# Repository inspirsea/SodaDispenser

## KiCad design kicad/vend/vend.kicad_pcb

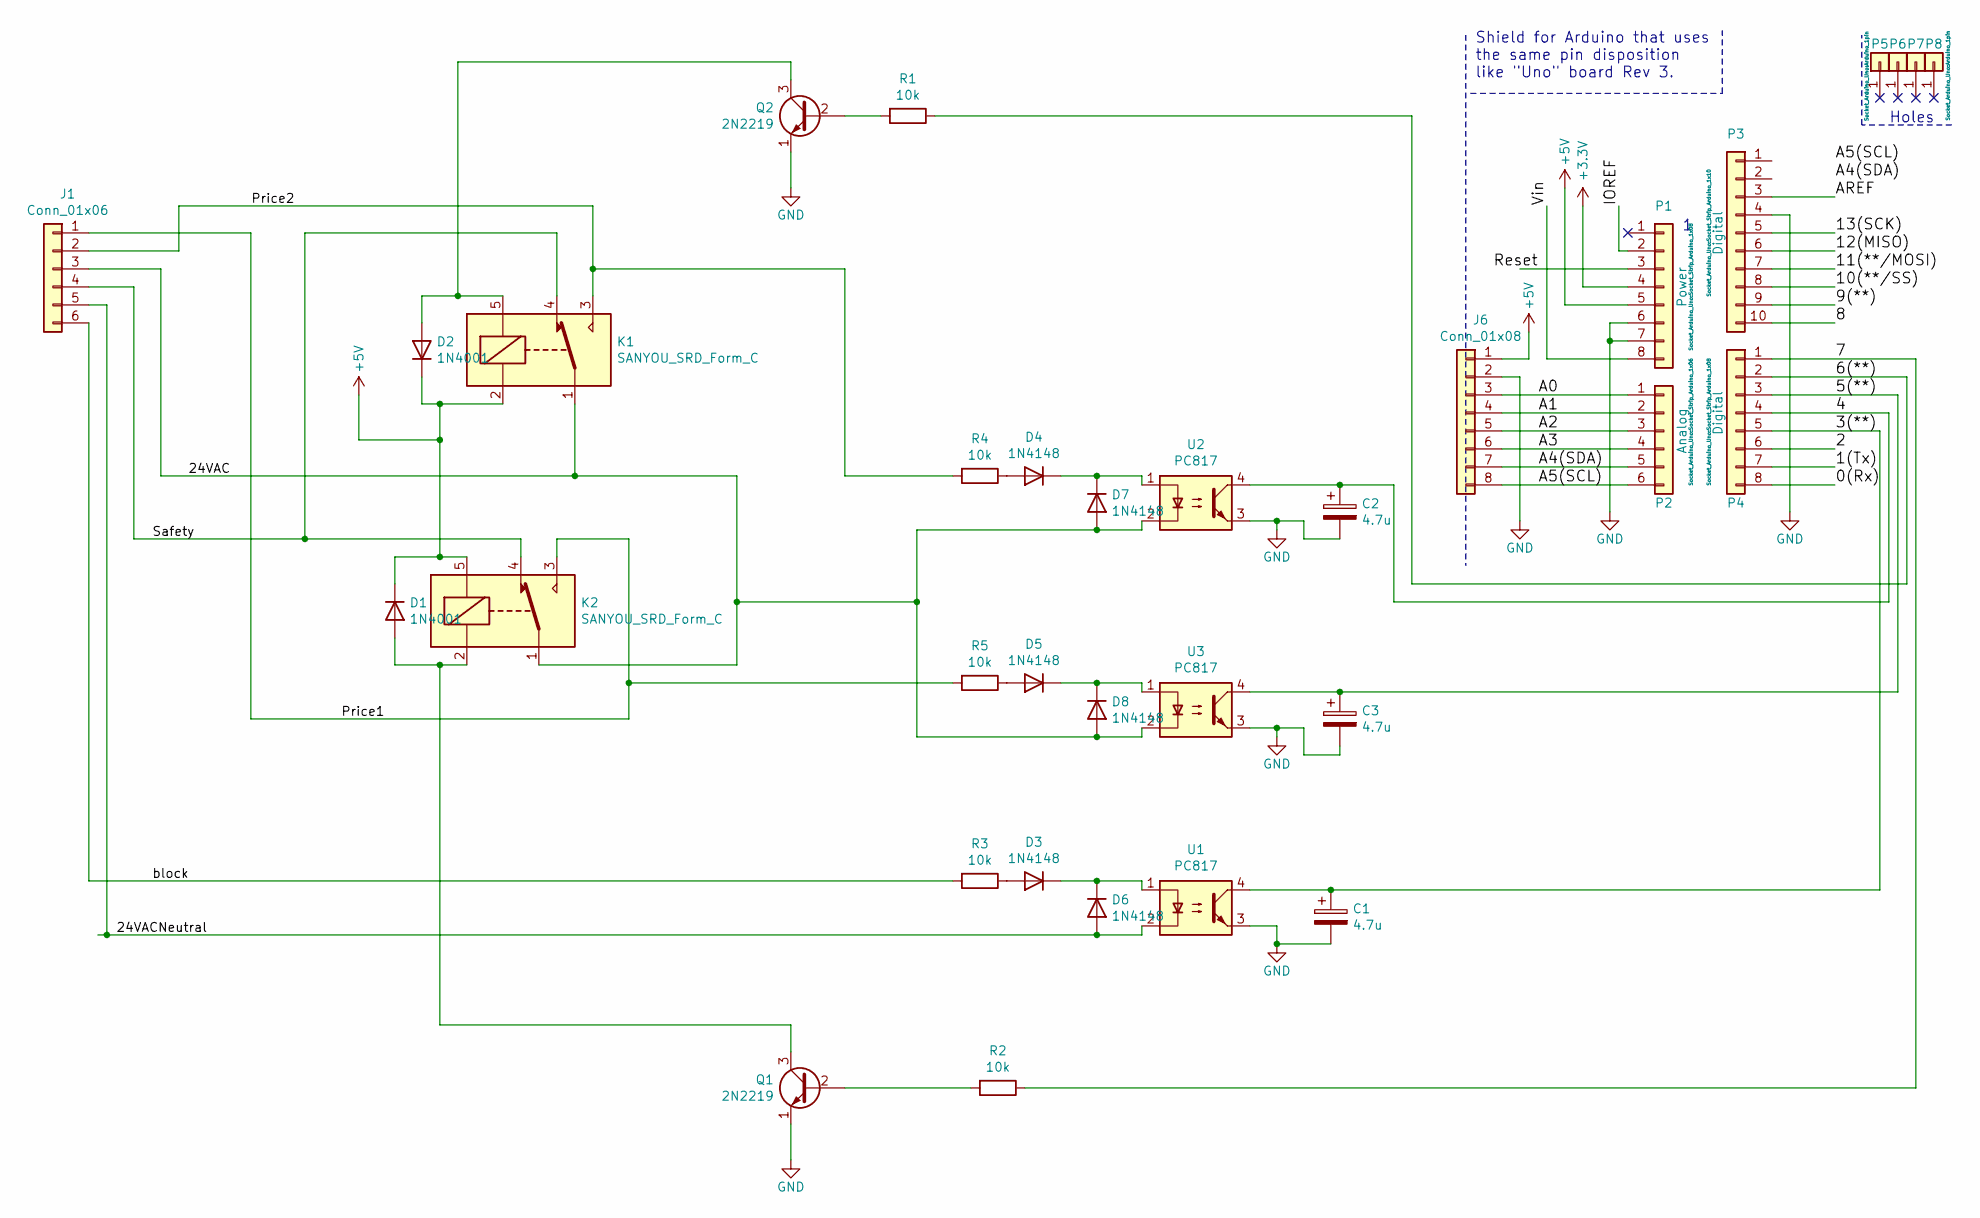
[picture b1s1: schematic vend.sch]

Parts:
C1, C2, C3: 4.7u; CP_Radial_D6.3mm_P2.50mm
D1, D2: 1N4001; D_DO-41_SOD81_P10.16mm_Horizontal
D3, D4, D5, D6, D7, D8: 1N4148; D_DO-35_SOD27_P7.62mm_Horizontal
J1: Conn_01x06; TerminalBlock_bornier-6_P5.08mm
J6: Conn_01x08; PinHeader_1x08_P2.54mm_Vertical
K1, K2: SANYOU_SRD_Form_C; Relay_SPDT_SANYOU_SRD_Series_Form_C
P1: Power; Socket_Strip_Arduino_1x08
P2: Analog; Socket_Strip_Arduino_1x06
P3: Digital; Socket_Strip_Arduino_1x10
P4: Digital; Socket_Strip_Arduino_1x08
P5, P6, P7, P8: CONN_01X01; Arduino_1pin
Q1, Q2: 2N2219; TO-92_Wide
R1, R2, R3, R4, R5: 10k; R_Axial_DIN0207_L6.3mm_D2.5mm_P7.62mm_Horizontal
U1, U2, U3: PC817; DIP-4_W7.62mm

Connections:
+3V3: P1.4
+5V: D1.1 (K), D2.1 (K), J6.1, K1.2, K2.5, P1.5
/0(Rx): P4.8
/1(Tx): P4.7
/2: P4.6
/3(**): C1.1, P4.5, U1.4
/4: C2.1, P4.4, U2.4
/5(**): C3.1, P4.3, U3.4
/6(**): P4.2, R1.1
/7: P4.1, R2.1
/8: P3.10
/9(**): P3.9
/10(**/SS): P3.8
/11(**/MOSI): P3.7
/12(MISO): P3.6
/13(SCK): P3.5
/24VAC: D7.2 (A), D8.2 (A), J1.3, K1.1, K2.1, U2.2, U3.2
/24VACNeutral: D6.2 (A), J1.5, U1.2
/A0: J6.3, P2.1
/A1: J6.4, P2.2
/A2: J6.5, P2.3
/A3: J6.6, P2.4
/A4(SDA): J6.7, P2.5
/A5(SCL): J6.8, P2.6
/AREF: P3.3
/IOREF: P1.2
/Price1: J1.1, K2.3, R5.2
/Price2: J1.2, K1.3, R4.2
/Safety: J1.4, K1.4, K2.4
/Vin: P1.8
/block: J1.6, R3.2
GND: C1.2, C2.2, C3.2, J6.2, P1.6, P1.7, P3.4, Q1.1 (E), Q2.1 (E), U1.3, U2.3, U3.3
unnamed: D1.2 (A), K2.2, Q1.3 (C)
unnamed: D2.2 (A), K1.5, Q2.3 (C)
unnamed: D3.1 (K), D6.1 (K), U1.1
unnamed: D3.2 (A), R3.1
unnamed: D4.1 (K), D7.1 (K), U2.1
unnamed: D4.2 (A), R4.1
unnamed: D5.1 (K), D8.1 (K), U3.1
unnamed: D5.2 (A), R5.1
unnamed: Q1.2 (B), R2.2
unnamed: Q2.2 (B), R1.2

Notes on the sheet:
Holes
Shield for Arduino that uses the same pin disposition like "Uno" board Rev 3.

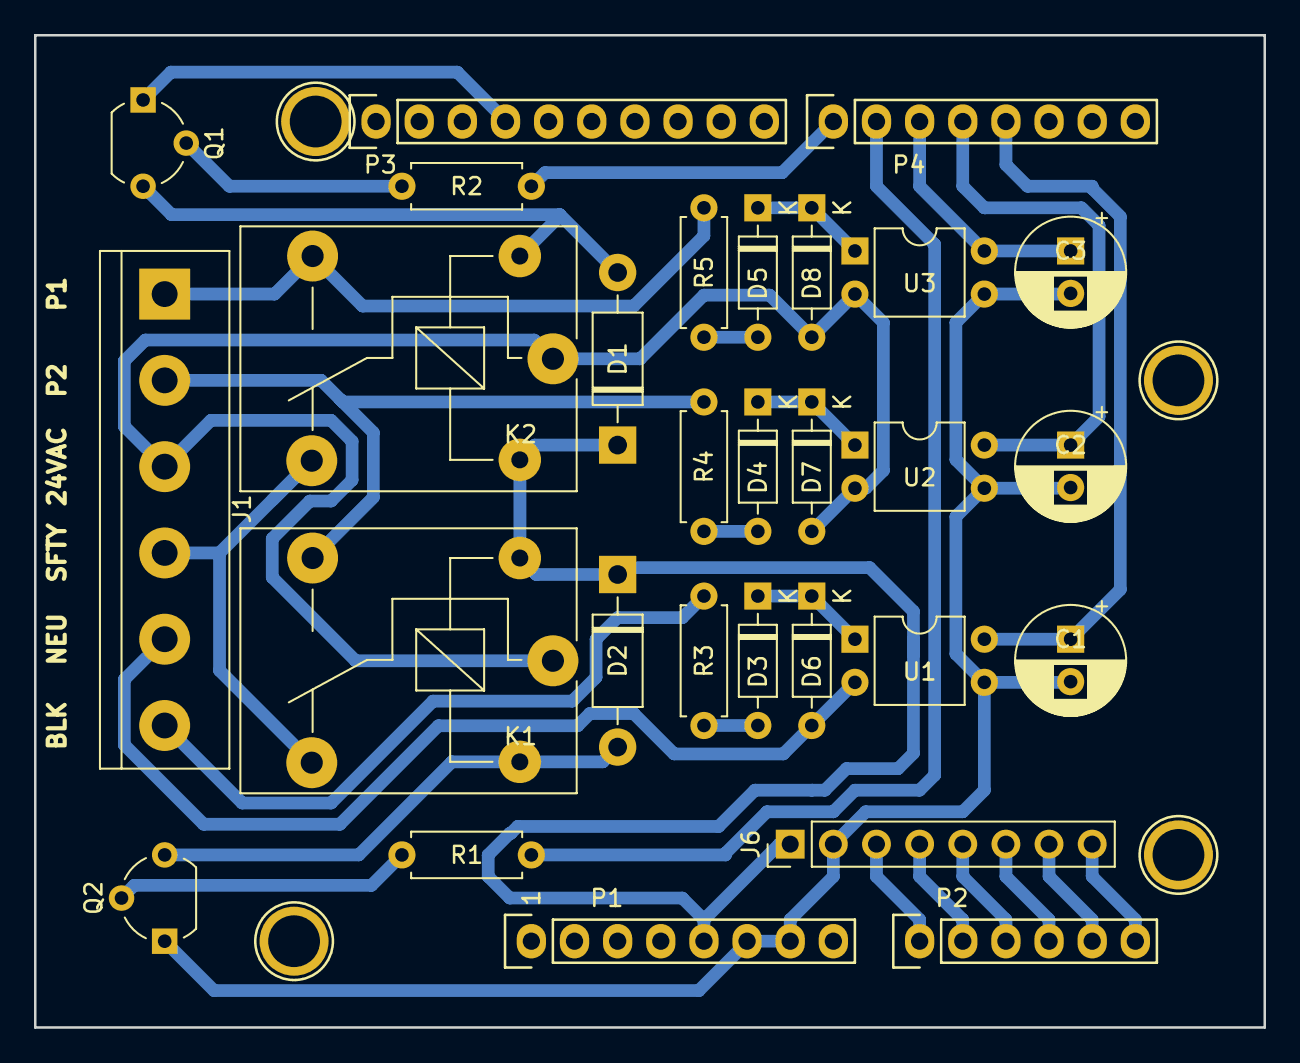
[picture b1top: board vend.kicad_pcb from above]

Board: 2 copper layers, 72.4 x 58.4 mm, 33 parts (0 on the bottom side), 29 nets.

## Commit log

2020-12-22 Fix init
2020-12-22 Added some example code
2020-12-22 Add LCD library
2020-12-25 Added code to save a 4 byte id and search for an id
2020-12-28 Wrap around if out of eprom memory
2020-12-30 Added rfid support
2020-12-30 Added library for rfid might need to remove some files...
2021-01-12 Cleanup
2021-01-14 FSM first commit
